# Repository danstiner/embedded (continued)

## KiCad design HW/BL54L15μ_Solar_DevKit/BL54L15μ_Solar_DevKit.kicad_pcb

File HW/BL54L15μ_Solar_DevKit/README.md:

## BOM

+------------------+-----+--------------------+-----------------------------------------+---------------------------------------------------------------------+
|    Reference     | Qty |       Value        |               Part Number               |                              Footprint                              |
+------------------+-----+--------------------+-----------------------------------------+---------------------------------------------------------------------+
| C1,C5            |   2 | 1μF                | CL05A105KA5NQNC                         | Capacitor_SMD:C_0402_1005Metric                                     |
| C2,C4,C7,C10,C11 |   5 | 10μF               | CL10A106KP8NNNC                         | Capacitor_SMD:C_0603_1608Metric                                     |
| C3               |   1 | 10uF               | CL10A106KP8NNNC                         | Capacitor_SMD:C_0603_1608Metric                                     |
| C6               |   1 | 2.2μF              | CL05A225KP5NSNC                         | Capacitor_SMD:C_0402_1005Metric                                     |
| C8,C9            |   2 | 1μF                | CL10A105KP8NNNC                         | Capacitor_SMD:C_0603_1608Metric                                     |
| C12              |   1 | 100nF              | CL05B103KB5NNNC                         | Capacitor_SMD:C_0402_1005Metric                                     |
| D1               |   1 | PWRLED             | 150060GS75000                           | LED_SMD:LED_0603_1608Metric                                         |
| D2               |   1 | PWRLED             | 150060SS75000                           | LED_SMD:LED_0603_1608Metric                                         |
| D3               |   1 | WL-SFTW_3528_PLCC6 | 150352M173300                           | 150352M173300:WL-SFTW_3528_PLCC6                                    |
| IC1              |   1 | nrf54L 453-00223R  | 453-00223R                              | Ezurio 453-00223R:45300223R                                         |
| J1               |   1 | Conn_Qwiic_1       | BM04B-SRSS-TB                           | Connector_JST:JST_SH_BM04B-SRSS-TB_1x04-1MP_P1.00mm_Vertical        |
| J2               |   1 | USB_C_Receptacle   | USB4056-03-A                            | USB4056_03_A:GCT_USB4056-03-A_REVA2                                 |
| J3,J4            |   2 | Conn_01x12_Pin     |                                         | Connector_PinHeader_2.54mm_SilkFree:PinHeader_1x12_P2.54mm_Vertical |
| J5               |   1 | Conn_01x02         |                                         | Connector_PinHeader_2.54mm:PinHeader_1x03_P2.54mm_Vertical          |
| J6,J7            |   2 | Conn_01x02         | B2B-PH-K-S                              | Connector_JST:JST_PH_B2B-PH-K_1x02_P2.00mm_Vertical                 |
| J8               |   1 | Conn_Qwiic_2       | BM04B-SRSS-TB                           | Connector_JST:JST_SH_BM04B-SRSS-TB_1x04-1MP_P1.00mm_Vertical        |
| L1,L2            |   2 | 2.2 μH             | CIGT201610EH2R2MNE                      | CIGT201610EH2R2MNE:IND_CIGT2016_SAM                                 |
| R1               |   1 | 2kΩ                | RC0402FR-132KL                          | Resistor_SMD:R_0402_1005Metric                                      |
| R2               |   1 | 250-500 kΩ         | RC0603JR-07330KL                        | Resistor_SMD:R_0603_1608Metric                                      |
| R3               |   1 | 47 kΩ              | RC0603FR-0747KL                         | Resistor_SMD:R_0603_1608Metric                                      |
| R4               |   1 | 100Ω               | RC0603FR-07100RL                        | Resistor_SMD:R_0603_1608Metric                                      |
| SW1              |   1 | Button0            | SKRKAHE020                              | Button_Switch_SMD:SW_Push_SPST_NO_Alps_SKRK                         |
| SW2              |   1 | Reset              | SKRKAHE020                              | Button_Switch_SMD:SW_Push_SPST_NO_Alps_SKRK                         |
| U1               |   1 | NPM1304-QEAA       | NPM1304-QEAA-R7                         | Package_QFN:QFN-32-1EP_5x5mm_P0.5mm_EP3.6x3.6mm_10milThermalVias    |
| X1               |   1 | 32.768 kHz         | CM7V-T1A-LOW-ESR-32.768KHZ-9PF-20-TA-QC | Crystal:Crystal_SMD_2012-2Pin_2.0x1.2mm                             |
+------------------+-----+--------------------+-----------------------------------------+---------------------------------------------------------------------+

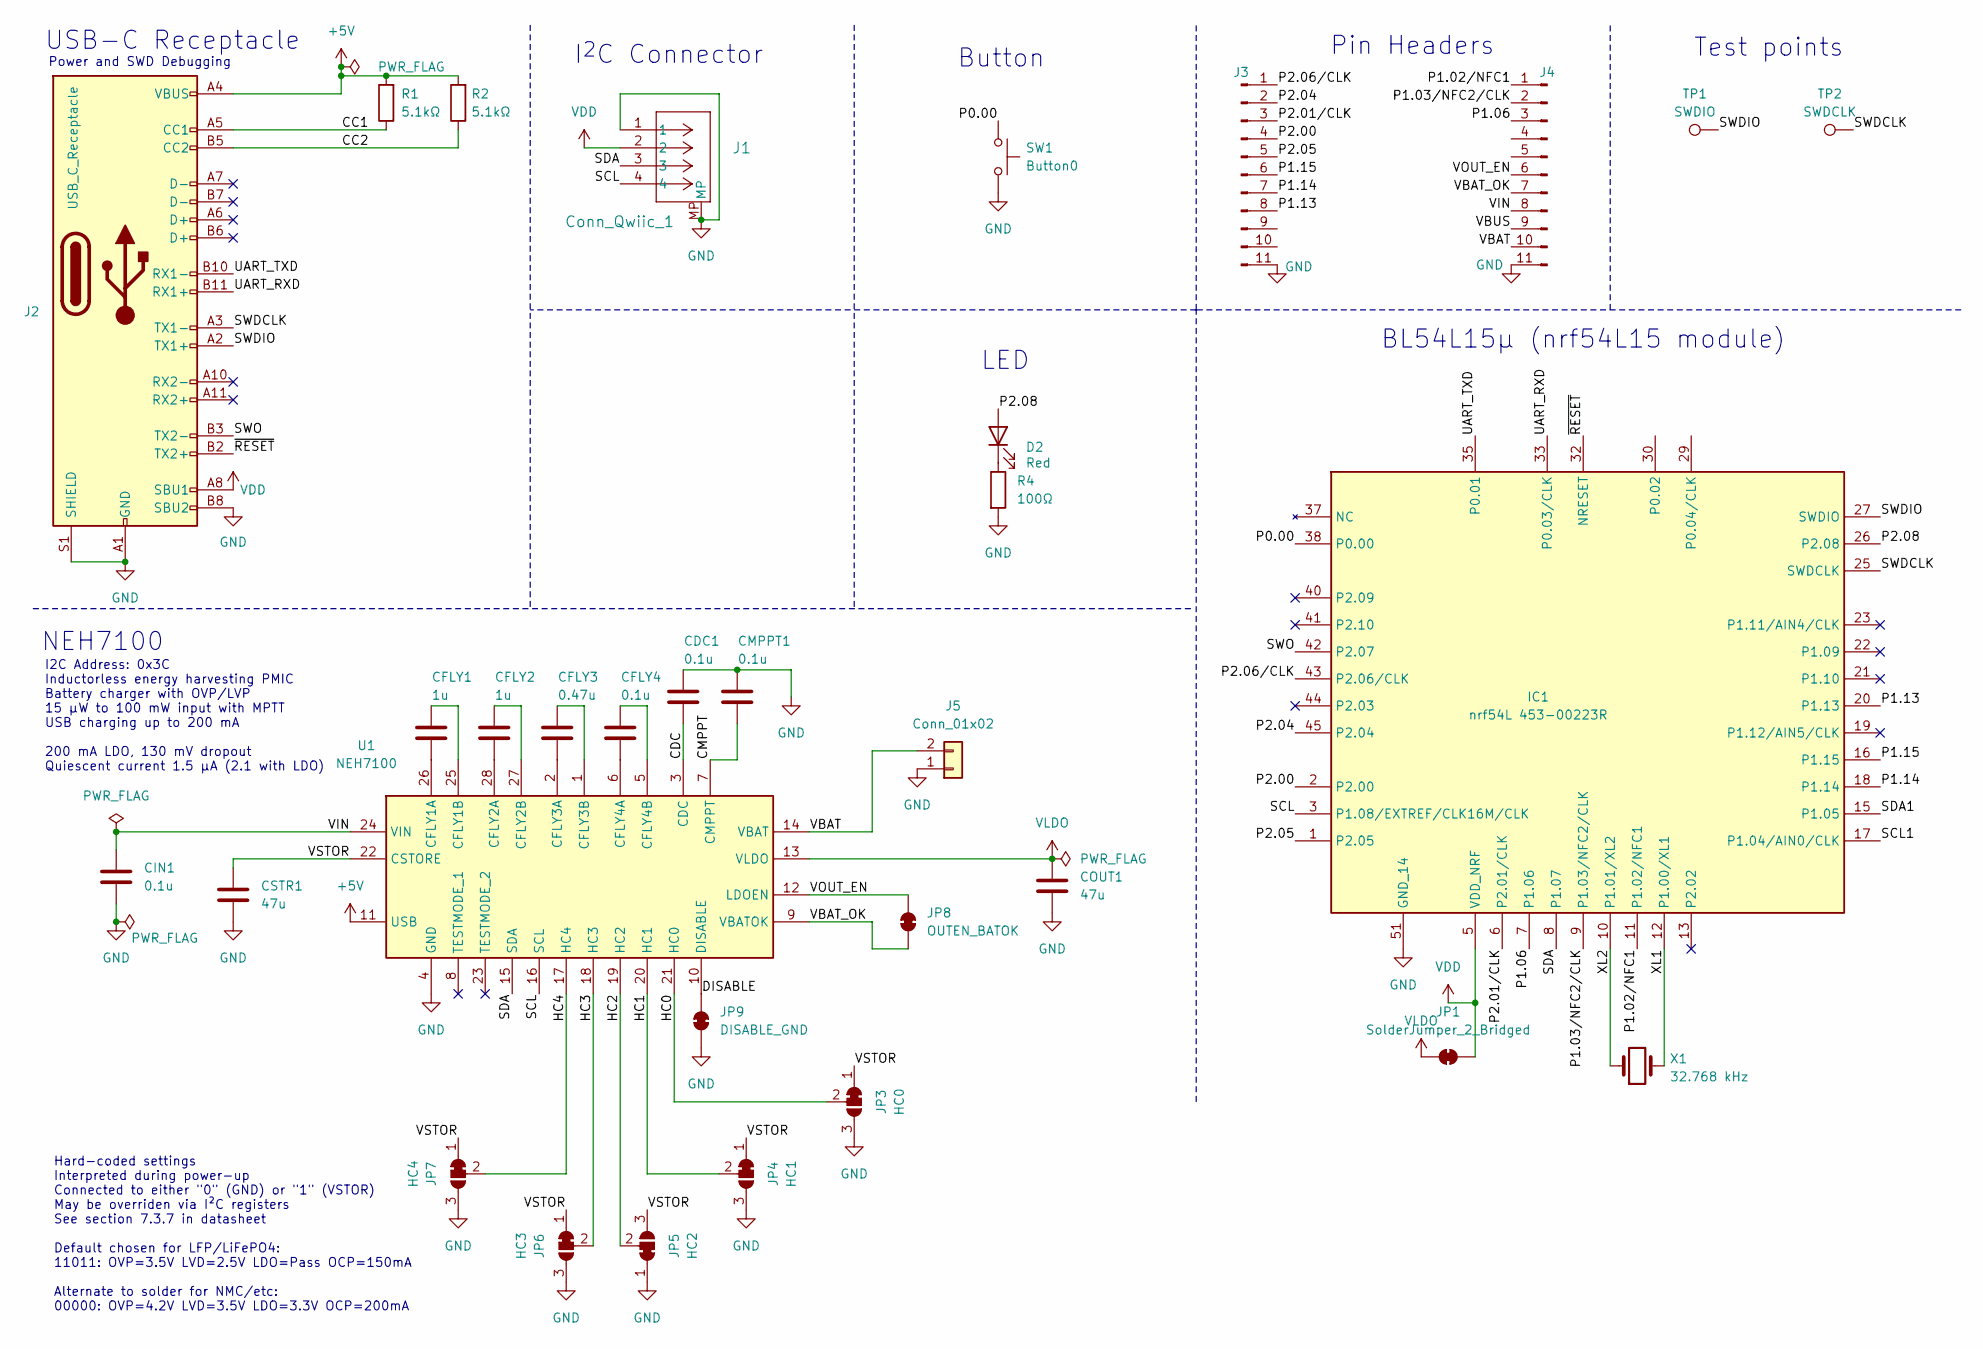
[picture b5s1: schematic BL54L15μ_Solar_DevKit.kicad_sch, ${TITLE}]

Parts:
CDC1: 0.1u; C_0402_1005Metric; Part Number GRM155R61A104KA01J
CFLY1, CFLY2: 1u; C_0402_1005Metric; Part Number GRM153R61A105ME95D
CFLY3: 0.47u; C_0402_1005Metric; Part Number GRM155R61A474KE15D
CFLY4: 0.1u; C_0402_1005Metric; Part Number GRM155R61A104KA01J
CIN1: 0.1u; C_0402_1005Metric; Part Number GRM155R61A104KA01J
CMPPT1: 0.1u; C_0402_1005Metric; Part Number GRM155R61A104KA01J
COUT1: 47u; C_0603_1608Metric; Part Number GRM188R60J476ME15D
CSTR1: 47u; C_0603_1608Metric; Part Number GRM188R60J476ME15D
D2: PWRLED; LED_0603_1608Metric; Part Number 150060SS75000
IC1: nrf54L 453-00223R; 45300223R; Part Number 453-00223R
J1: Conn_Qwiic_1; JST_SH_BM04B-SRSS-TB_1x04-1MP_P1.00mm_Vertical; Part Number BM04B-SRSS-TB
J2: USB_C_Receptacle; GCT_USB4056-03-A_REVA2; Part Number USB4056-03-A
J3, J4: Conn_01x12_Pin; PinHeader_1x11_P2.54mm_Vertical
J5: Conn_01x02; JST_PH_B2B-PH-K_1x02_P2.00mm_Vertical
JP1: SolderJumper_2_Bridged
JP3: HC0; SolderJumper-3_P1.3mm_Bridged12_RoundedPad1.0x1.5mm
JP4: HC1; SolderJumper-3_P1.3mm_Bridged12_RoundedPad1.0x1.5mm
JP5: HC2; SolderJumper-3_P1.3mm_Bridged12_RoundedPad1.0x1.5mm
JP6: HC3; SolderJumper-3_P1.3mm_Bridged12_RoundedPad1.0x1.5mm
JP7: HC4; SolderJumper-3_P1.3mm_Bridged12_RoundedPad1.0x1.5mm
JP8: OUTEN_BATOK; SolderJumper-2_P1.3mm_Bridged_RoundedPad1.0x1.5mm
JP9: DISABLE_GND; SolderJumper-2_P1.3mm_Bridged_RoundedPad1.0x1.5mm
R1, R2: 5.1kΩ
R4: 100Ω; R_0603_1608Metric; Part Number RC0603FR-07100RL
SW1: Button0; SW_Push_SPST_NO_Alps_SKRK; Part Number SKRKAHE020; Digikey Part Number 4809-SKRKAHE020CT-ND
TP1: SWDIO; TestPoint_Pad_D1.0mm
TP2: SWDCLK; TestPoint_Pad_D1.0mm
U1: NEH7100; QFN40P400X400X90-29N-D; Mouser Part Number 771-NEH7100BUHP
X1: 32.768 kHz; Crystal_SMD_2012-2Pin_2.0x1.2mm; Part Number CM7V-T1A-LOW-ESR-32.768KHZ-9PF-20-TA-QC

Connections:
+5V: J2.A4 (VBUS), J2.A9 (VBUS), J2.B4 (VBUS), J2.B9 (VBUS), R1.2, R2.2, U1.11 (USB)
/CC1: J2.A5 (CC1), R1.1
/CC2: J2.B5 (CC2), R2.1
/CDC: CDC1.2, U1.3 (CDC)
/CMPPT: CMPPT1.2, U1.7 (CMPPT)
/DISABLE: JP9.2 (B), U1.10 (DISABLE)
/HC0: JP3.2 (C), U1.21 (HC0)
/HC1: JP4.2 (C), U1.20 (HC1)
/HC2: JP5.2 (C), U1.19 (HC2)
/HC3: JP6.2 (C), U1.18 (HC3)
/HC4: JP7.2 (C), U1.17 (HC4)
/P0.00: IC1.38 (P0.00), SW1.1
/P1.02/NFC1: IC1.11 (P1.02/NFC1), J4.1
/P1.03/NFC2/CLK: IC1.9 (P1.03/NFC2/CLK), J4.2
/P1.06: IC1.7 (P1.06), J4.3
/P1.13: IC1.20 (P1.13), J3.8
/P1.14: IC1.18 (P1.14), J3.7
/P1.15: IC1.16 (P1.15), J3.6
/P2.00: IC1.2 (P2.00), J3.4
/P2.01/CLK: IC1.6 (P2.01/CLK), J3.3
/P2.04: IC1.45 (P2.04), J3.2
/P2.05: IC1.1 (P2.05), J3.5
/P2.06/CLK: IC1.43 (P2.06/CLK), J3.1
/P2.08: D2.2 (A), IC1.26 (P2.08)
/SCL: IC1.3 (P1.08/EXTREF/CLK16M/CLK), J1.4, U1.16 (SCL)
/SCL1: IC1.17 (P1.04/AIN0/CLK)
/SCL2: IC1.29 (P0.04/CLK)
/SDA: IC1.8 (P1.07), J1.3, U1.15 (SDA)
/SDA1: IC1.15 (P1.05)
/SDA2: IC1.30 (P0.02)
/SWDCLK: IC1.25 (SWDCLK), J2.A3 (TX1-), TP2.1
/SWDIO: IC1.27 (SWDIO), J2.A2 (TX1+), TP1.1
/SWO: IC1.42 (P2.07), J2.B3 (TX2-)
/VBAT: J4.10, J5.2, U1.14 (VBAT)
/VBAT_OK: J4.7, JP8.1 (A), U1.9 (VBATOK)
/VBUS: J4.9
/VIN: CIN1.1, J4.8, U1.24 (VIN)
/VOUT_EN: J4.6, JP8.2 (B), U1.12 (LDOEN)
/VSTOR: CSTR1.1, JP3.1 (A), JP4.1 (A), JP5.3 (B), JP6.1 (A), JP7.1 (A), U1.22 (CSTORE)
/XL1: IC1.12 (P1.00/XL1), X1.2
/XL2: IC1.10 (P1.01/XL2), X1.1
/~RESET: IC1.32 (NRESET), J2.B2 (TX2+)
GND: CDC1.1, CIN1.2, CMPPT1.1, COUT1.2, CSTR1.2, IC1.4 (GND_1), IC1.14 (GND_2), IC1.24 (GND_3), IC1.28 (GND_4), IC1.31 (GND_5), IC1.34 (GND_6), IC1.36 (GND_7), IC1.39 (GND_8), IC1.46 (GND_9), IC1.47 (GND_10), IC1.48 (GND_11), IC1.49 (GND_12), IC1.50 (GND_13), IC1.51 (GND_14), J1.1, J1.MP, J2.A1 (GND), J2.A12 (GND), J2.B1 (GND), J2.B8 (SBU2), J2.B12 (GND), J2.S1 (SHIELD), J3.11, J4.11, J5.1, JP3.3 (B), JP4.3 (B), JP5.1 (A), JP6.3 (B), JP7.3 (B), JP9.1 (A), R4.2, SW1.2, U1.4 (GND), U1.29 (GND_2)
unnamed: D2.1 (K), R4.1
unnamed: CFLY1.2, U1.26 (CFLY1A)
unnamed: CFLY1.1, U1.25 (CFLY1B)
unnamed: CFLY2.2, U1.28 (CFLY2A)
unnamed: CFLY2.1, U1.27 (CFLY2B)
unnamed: CFLY3.2, U1.2 (CFLY3A)
unnamed: CFLY3.1, U1.1 (CFLY3B)
unnamed: CFLY4.2, U1.6 (CFLY4A)
unnamed: CFLY4.1, U1.5 (CFLY4B)
VDD: IC1.5 (VDD_NRF), J1.2, J2.A8 (SBU1), JP1.2 (B)
VLDO: COUT1.1, JP1.1 (A), U1.13 (VLDO)

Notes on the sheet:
I2C Address: 0x3C Inductorless energy harvesting PMIC Battery charger with OVP/LVP 15 μW to 100 mW input with MPTT USB charging up to 200 mA 200 mA LDO, 130 mV dropout Quiescent current 1.5 μA (2.1 with LDO)
I^{2}C Connector
USB-C Receptacle
Button
BL54L15μ (nrf54L15 module)
Test points
Pin Headers
Power and SWD Debugging
LED
NEH7100
Hard-coded settings Interpreted during power-up Connected to either "0" (GND) or "1" (VSTOR) May be overriden via I²C registers See section 7.3.7 in datasheet Default chosen for LFP/LiFePO4: 11011: OVP=3.5V LVD=2.5V LDO=Pass OCP=150mA Alternate to solder for NMC/etc: 00000: OVP=4.2V LVD=3.5V LDO=3.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

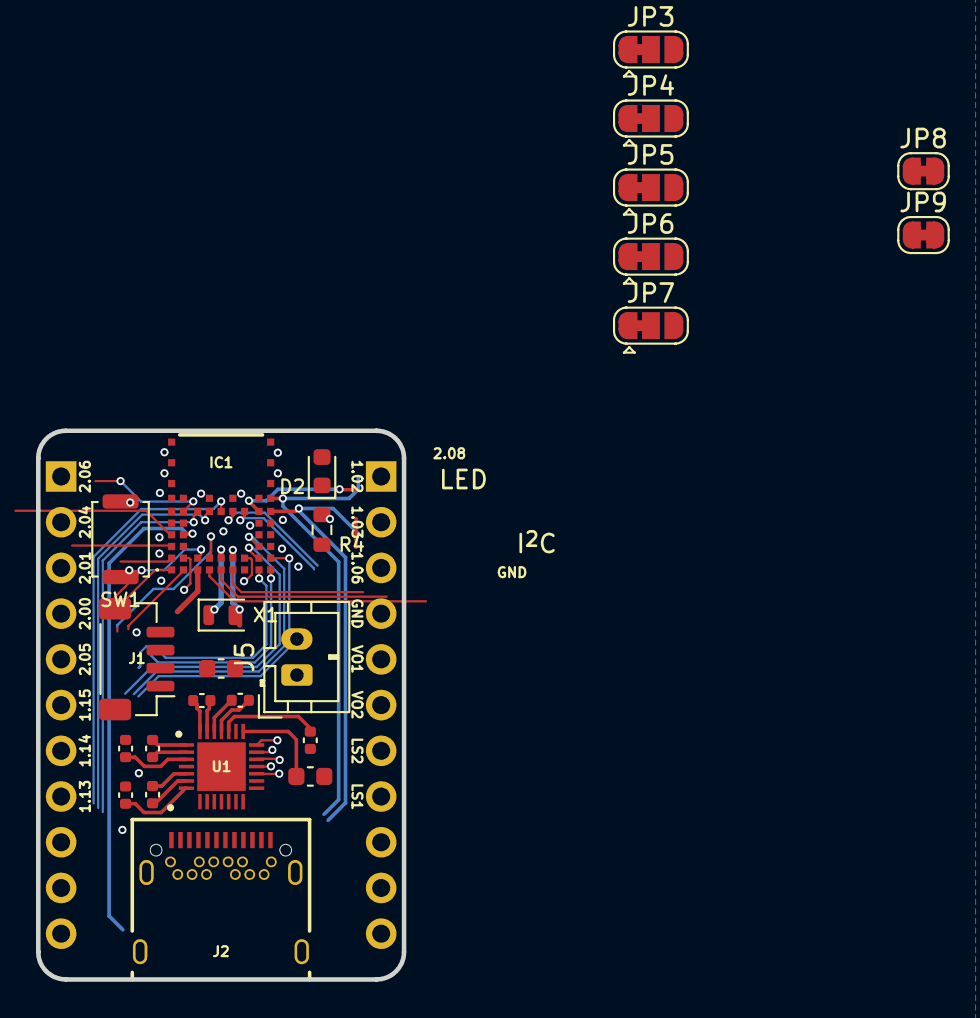
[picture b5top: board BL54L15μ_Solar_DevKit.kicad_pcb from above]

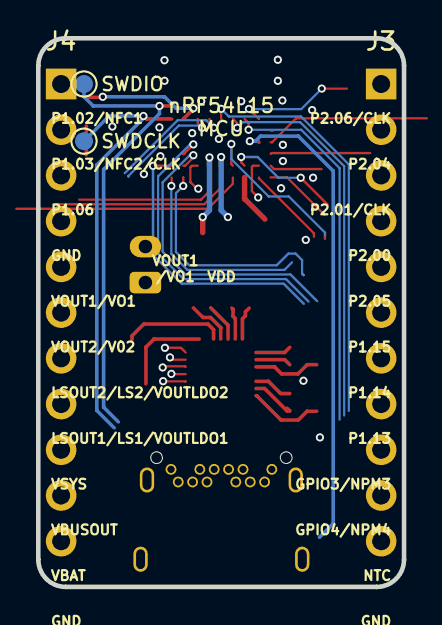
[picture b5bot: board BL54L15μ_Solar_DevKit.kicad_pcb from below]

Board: 4 copper layers, 20.3 x 30.5 mm, 29 parts (4 on the bottom side), 47 nets.

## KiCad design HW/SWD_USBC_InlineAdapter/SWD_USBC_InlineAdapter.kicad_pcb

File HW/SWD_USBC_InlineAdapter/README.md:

## Bill of materials

+-----------+-----+----------------------+--------------------+------------------------------------------------------------------------+
| Reference | Qty | Value                | Part Number        | Footprint                                                              |
+-----------+-----+----------------------+--------------------+------------------------------------------------------------------------+
| D1        | 1   | RED LED              | 150060SS75000      | Diode_SMD:D_0603_1608Metric                                            |
| J1        | 1   | Conn_ARM_JTAG_SWD_10 | FTSH-105-01-F-DV-K | Connector_PinHeader_1.27mm:PinHeader_2x05_P1.27mm_Vertical_SMD         |
| J2        | 1   | Conn_01x04           | 0532610471         | Connector_Molex:Molex_PicoBlade_53261-0471_1x04-1MP_P1.25mm_Horizontal |
| J3        | 1   | USB_C_Receptacle     | USB4056-03-A       | USB4056_03_A:GCT_USB4056-03-A_REVA2                                    |
| P1        | 1   | USB_C_Plug           | USB4155-03-C       | USB4155_03_C:GCT_USB4155-03-C_REVA                                     |
| R1        | 1   | 100Ω                 | RC0603FR-07100RL   | Resistor_SMD:R_0603_1608Metric                                         |
| R2        | 1   | 22kΩ ±5%             | RC0603FR-1322KL    | Resistor_SMD:R_0603_1608Metric                                         |
| R3        | 1   | 10kΩ ±5%             | RC0603FR-0710KL    | Resistor_SMD:R_0603_1608Metric                                         |
| R4,R5     | 2   | 5.1k                 | RC0603FR-075K1L    | Resistor_SMD:R_0603_1608Metric                                         |
+-----------+-----+----------------------+--------------------+------------------------------------------------------------------------+

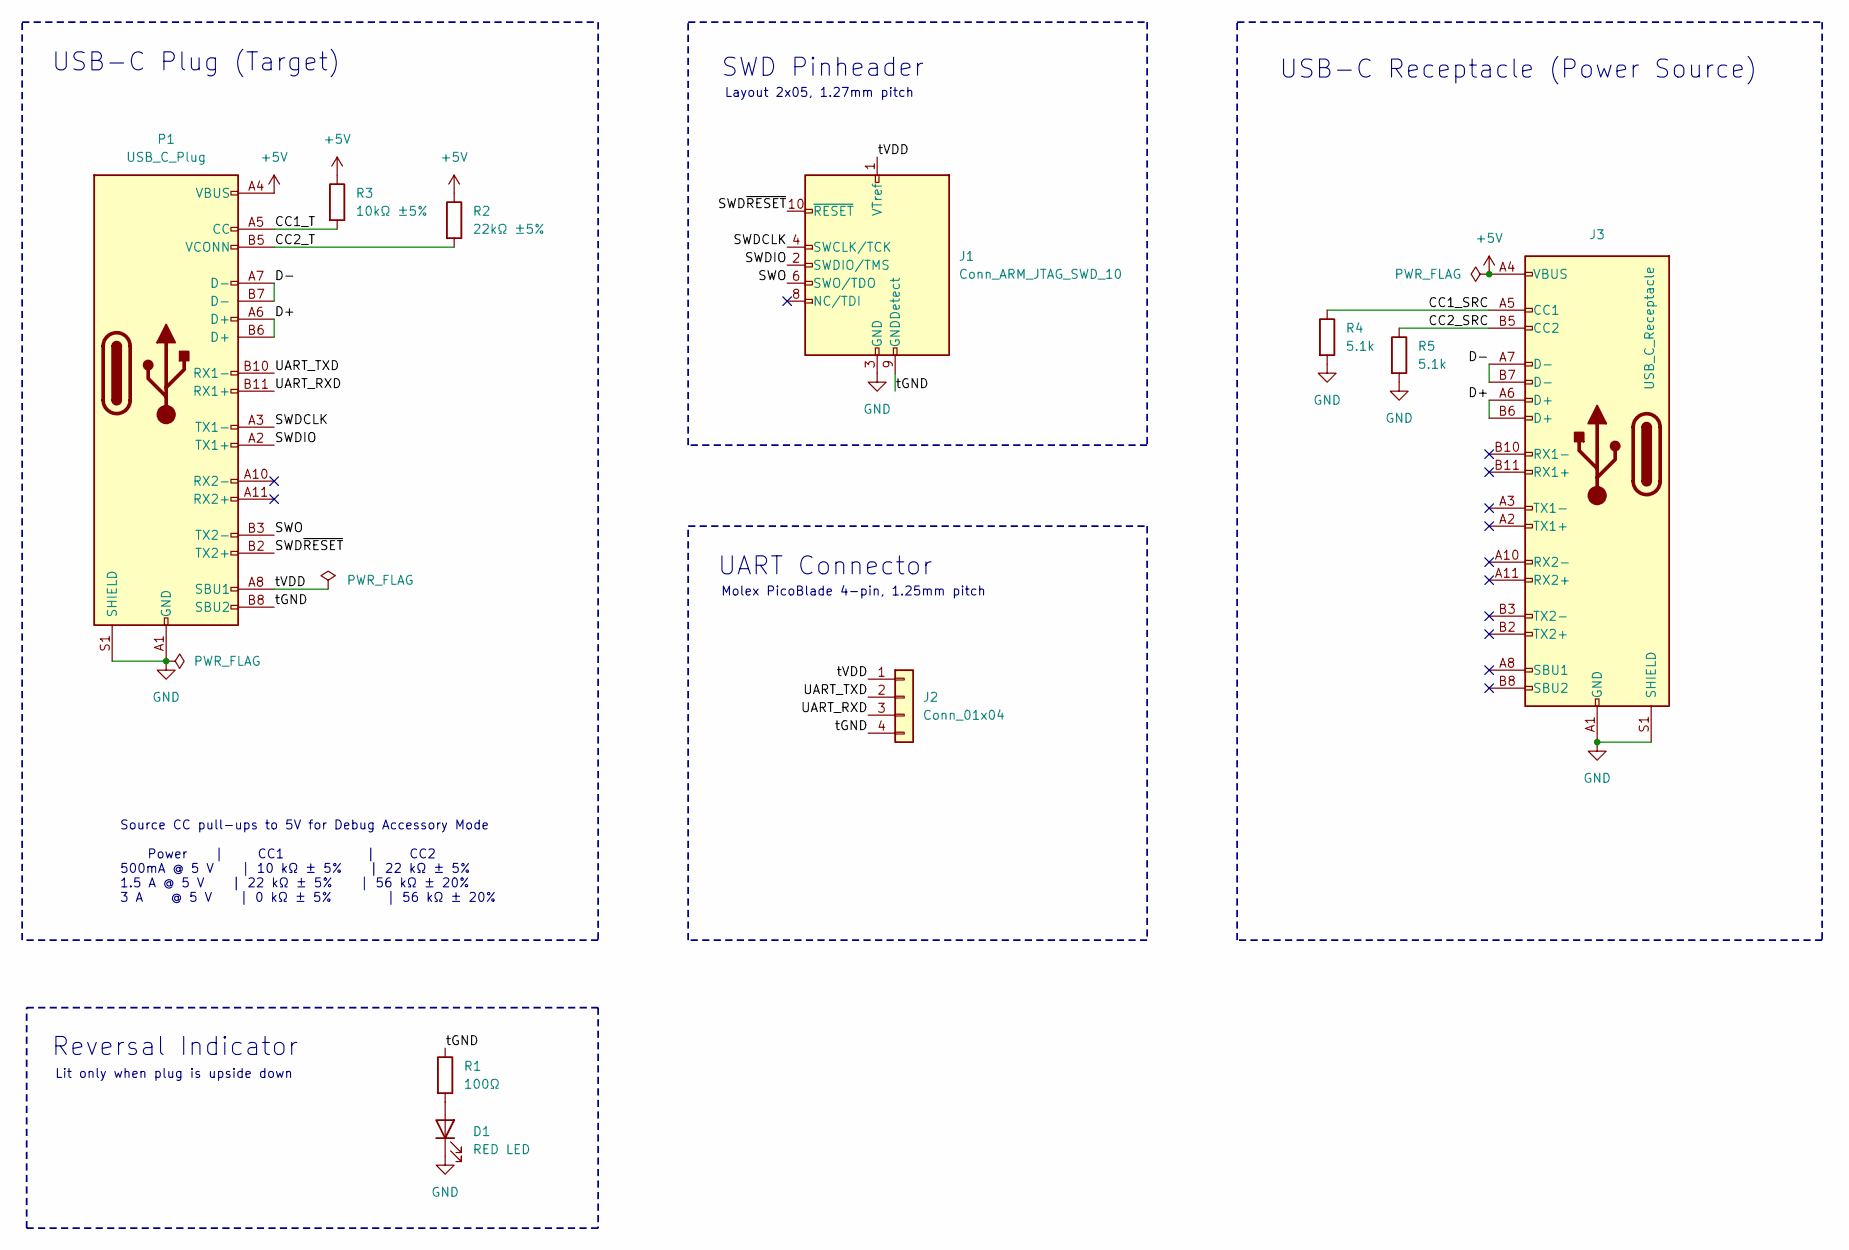
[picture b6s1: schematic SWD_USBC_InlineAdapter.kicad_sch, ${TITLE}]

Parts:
D1: RED LED; D_0603_1608Metric; Part Number 150060SS75000
J1: Conn_ARM_JTAG_SWD_10; PinHeader_2x05_P1.27mm_Vertical_SMD; Part Number FTSH-105-01-F-DV-K
J2: Conn_01x04; Molex_PicoBlade_53261-0471_1x04-1MP_P1.25mm_Horizontal; Part Number 0532610471
J3: USB_C_Receptacle; GCT_USB4056-03-A_REVA2; Part Number USB4056-03-A
P1: USB_C_Plug; GCT_USB4155-03-C_REVA; Part Number USB4155-03-C
R1: 100Ω; R_0603_1608Metric; Part Number RC0603FR-07100RL
R2: 22kΩ ±5%; R_0603_1608Metric; Digikey Part Number RC0603FR-1322KL
R3: 10kΩ ±5%; R_0603_1608Metric; Digikey Part Number RC0603FR-0710KL
R4, R5: 5.1k; R_0603_1608Metric; Digikey Part Number 311-5.10KHRCT-ND

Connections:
+5V: J3.A4 (VBUS), J3.A9 (VBUS), J3.B4 (VBUS), J3.B9 (VBUS), P1.A4 (VBUS), P1.A9 (VBUS), P1.B4 (VBUS), P1.B9 (VBUS), R2.1, R3.1
/CC1_SRC: J3.A5 (CC1), R4.1
/CC1_T: P1.A5 (CC), R3.2
/CC2_SRC: J3.B5 (CC2), R5.1
/CC2_T: P1.B5 (VCONN), R2.2
/D+: J3.A6 (D+), J3.B6 (D+), P1.A6 (D+), P1.B6 (D+)
/D-: J3.A7 (D-), J3.B7 (D-), P1.A7 (D-), P1.B7 (D-)
/SWDCLK: J1.4 (SWCLK/TCK), P1.A3 (TX1-)
/SWDIO: J1.2 (SWDIO/TMS), P1.A2 (TX1+)
/SWD~RESET: J1.10 (~RESET), P1.B2 (TX2+)
/SWO: J1.6 (SWO/TDO), P1.B3 (TX2-)
/UART_RXD: J2.3, P1.B11 (RX1+)
/UART_TXD: J2.2, P1.B10 (RX1-)
/tGND: J1.9 (GNDDetect), J2.4, P1.B8 (SBU2), R1.1
/tVDD: J1.1 (VTref), J2.1, P1.A8 (SBU1)
GND: D1.1 (K), J1.3 (GND), J1.5 (GND), J3.A1 (GND), J3.A12 (GND), J3.B1 (GND), J3.B12 (GND), J3.S1 (SHIELD), P1.A1 (GND), P1.A12 (GND), P1.B1 (GND), P1.B12 (GND), P1.S1 (SHIELD), R4.2, R5.2
unnamed: D1.2 (A), R1.2

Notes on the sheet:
SWD Pinheader
Layout 2x05, 1.27mm pitch
Reversal Indicator
Lit only when plug is upside down
USB-C Receptacle (Power Source)
Source CC pull-ups to 5V for Debug Accessory Mode Power | CC1 | CC2 500mA @ 5 V | 10 kΩ ± 5% | 22 kΩ ± 5% 1.5 A @ 5 V | 22 kΩ ± 5% | 56 kΩ ± 20% 3 A @ 5 V | 0 kΩ ± 5% | 56 kΩ ± 20%
USB-C Plug (Target)
UART Connector
Molex PicoBlade 4-pin, 1.25mm pitch

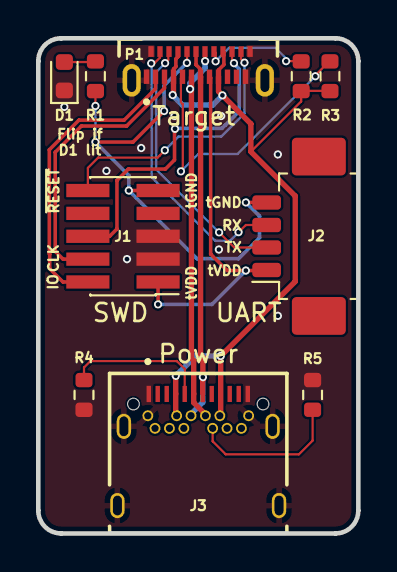
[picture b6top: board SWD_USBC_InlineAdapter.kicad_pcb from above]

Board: 4 copper layers, 17.8 x 27.5 mm, 10 parts (0 on the bottom side), 17 nets.

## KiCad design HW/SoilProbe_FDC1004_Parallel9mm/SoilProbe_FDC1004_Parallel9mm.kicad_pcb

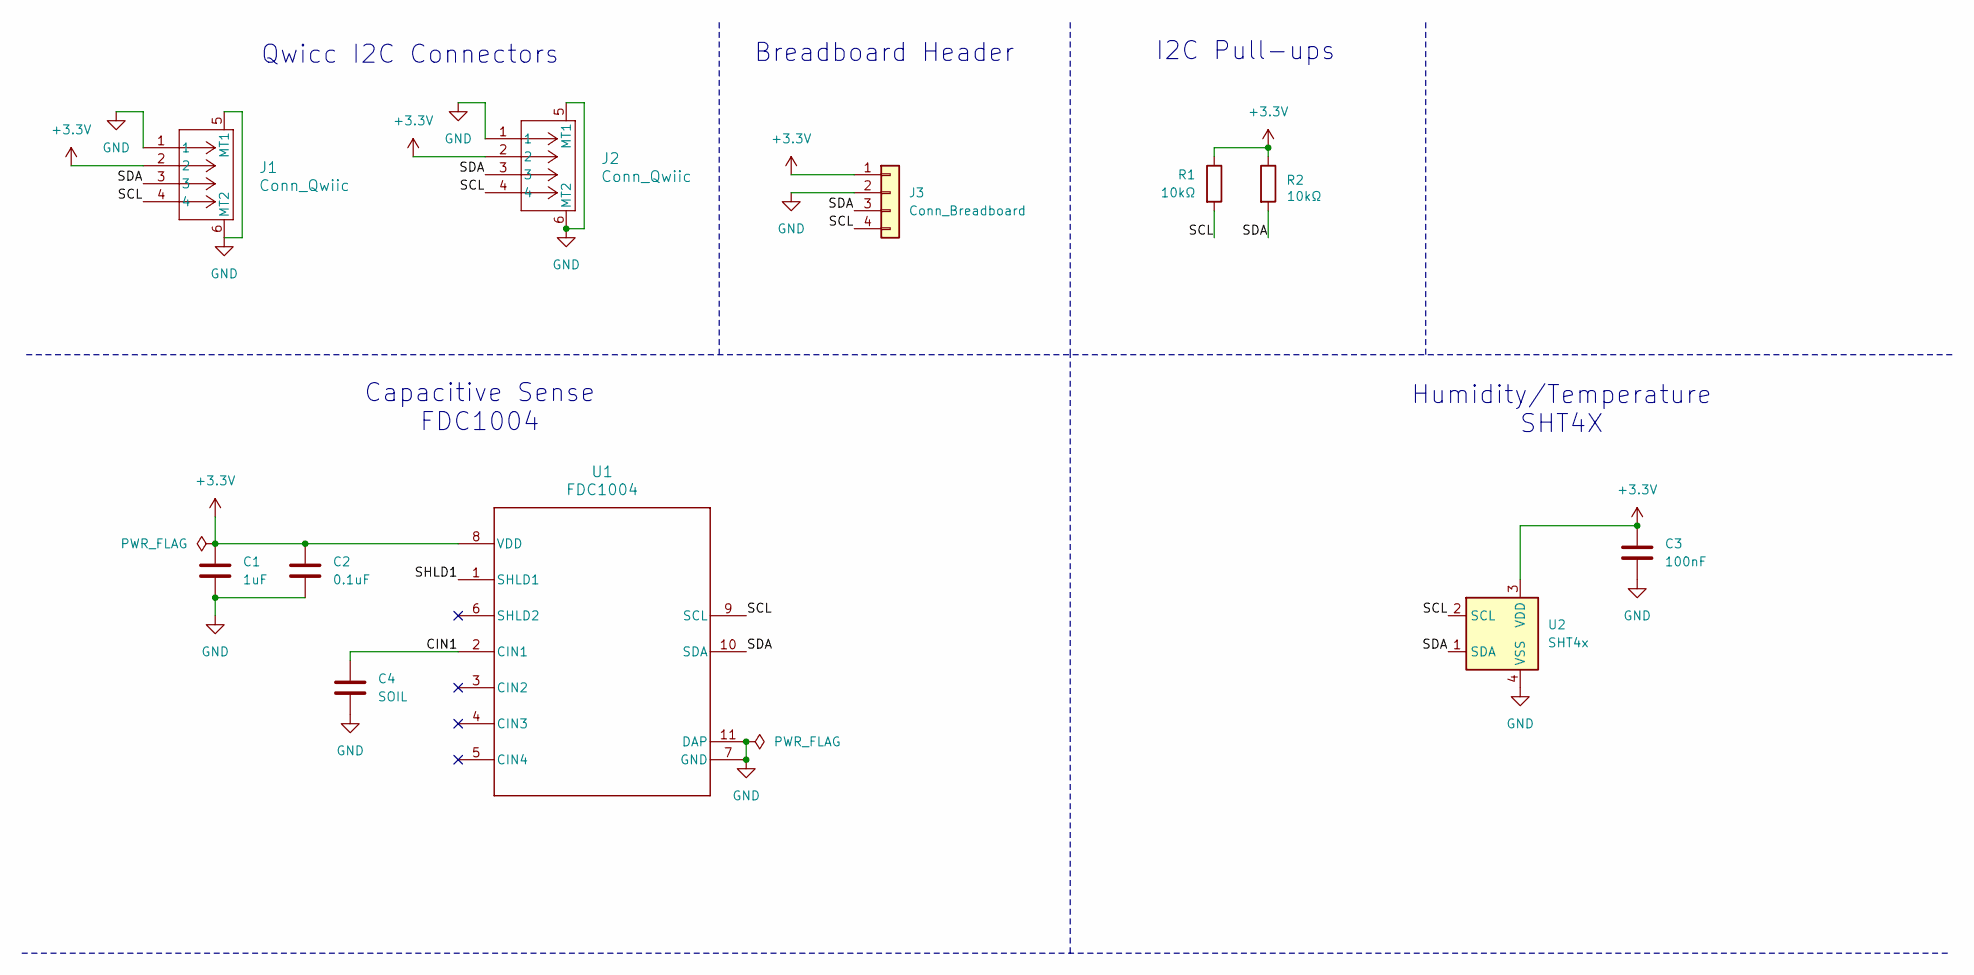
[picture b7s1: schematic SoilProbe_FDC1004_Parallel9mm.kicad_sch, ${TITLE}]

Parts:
C1: 1uF; C_0603_1608Metric; Manufacturer Part Number CL10A105KP8NNNC
C2: 0.1uF; C_0402_1005Metric; Manufacturer Part Number GRM155R61A104KA01J
C3: 100nF; C_0402_1005Metric; Part Number GRM155R61A104KA01J
C4: SOIL; C_Rectangle
J1, J2: Conn_Qwiic; CONN_SM04B-SRSS-TB_JST; Manufacturer Part Number SM04B-SRSS-TB; Digikey Part Number 455-SM04B-SRSS-TBCT-ND
J3: Conn_Breadboard; PinHeader_1x04_P2.54mm_Vertical
R1, R2: 10kΩ; R_0603_1608Metric; Manufacturer Part Number RC0603FR-0710KL
U1: FDC1004; DSC0010B_NV; Manufacturer Part Number FDC1004DSCR
U2: SHT4x; Sensirion_DFN-4_1.5x1.5mm_P0.8mm_SHT4x_NoCentralPad

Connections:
+3.3V: C1.1, C2.1, C3.1, J1.2, J2.2, J3.1, R1.1, R2.1, U1.8 (VDD), U2.3 (VDD)
/CIN1: C4.1, U1.2 (CIN1)
/SCL: J1.4, J2.4, J3.4, R1.2, U1.9 (SCL), U2.2 (SCL)
/SDA: J1.3, J2.3, J3.3, R2.2, U1.10 (SDA), U2.1 (SDA)
/SHLD1: U1.1 (SHLD1)
GND: C1.2, C2.2, C3.2, C4.2, J1.1, J1.5 (MT1), J1.6 (MT2), J2.1, J2.5 (MT1), J2.6 (MT2), J3.2, U1.7 (GND), U1.11 (DAP), U2.4 (VSS)

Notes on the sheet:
Breadboard Header
Qwicc I2C Connectors
Humidity/Temperature SHT4X
Capacitive Sense FDC1004
I2C Pull-ups

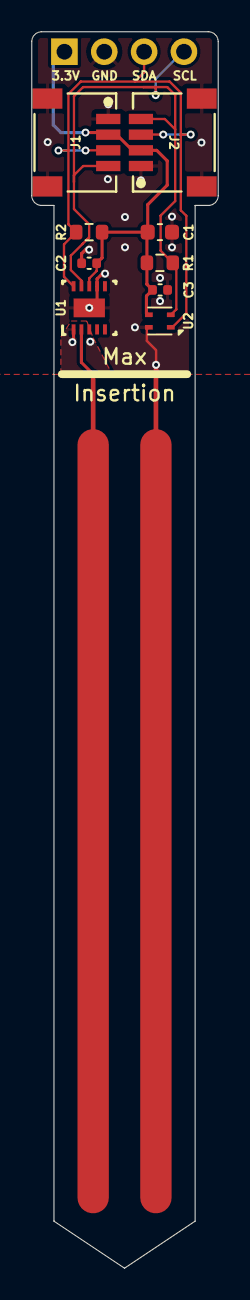
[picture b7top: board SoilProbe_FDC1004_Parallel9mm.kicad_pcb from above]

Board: 2 copper layers, 11.9 x 78.8 mm, 11 parts (0 on the bottom side), 5 nets.

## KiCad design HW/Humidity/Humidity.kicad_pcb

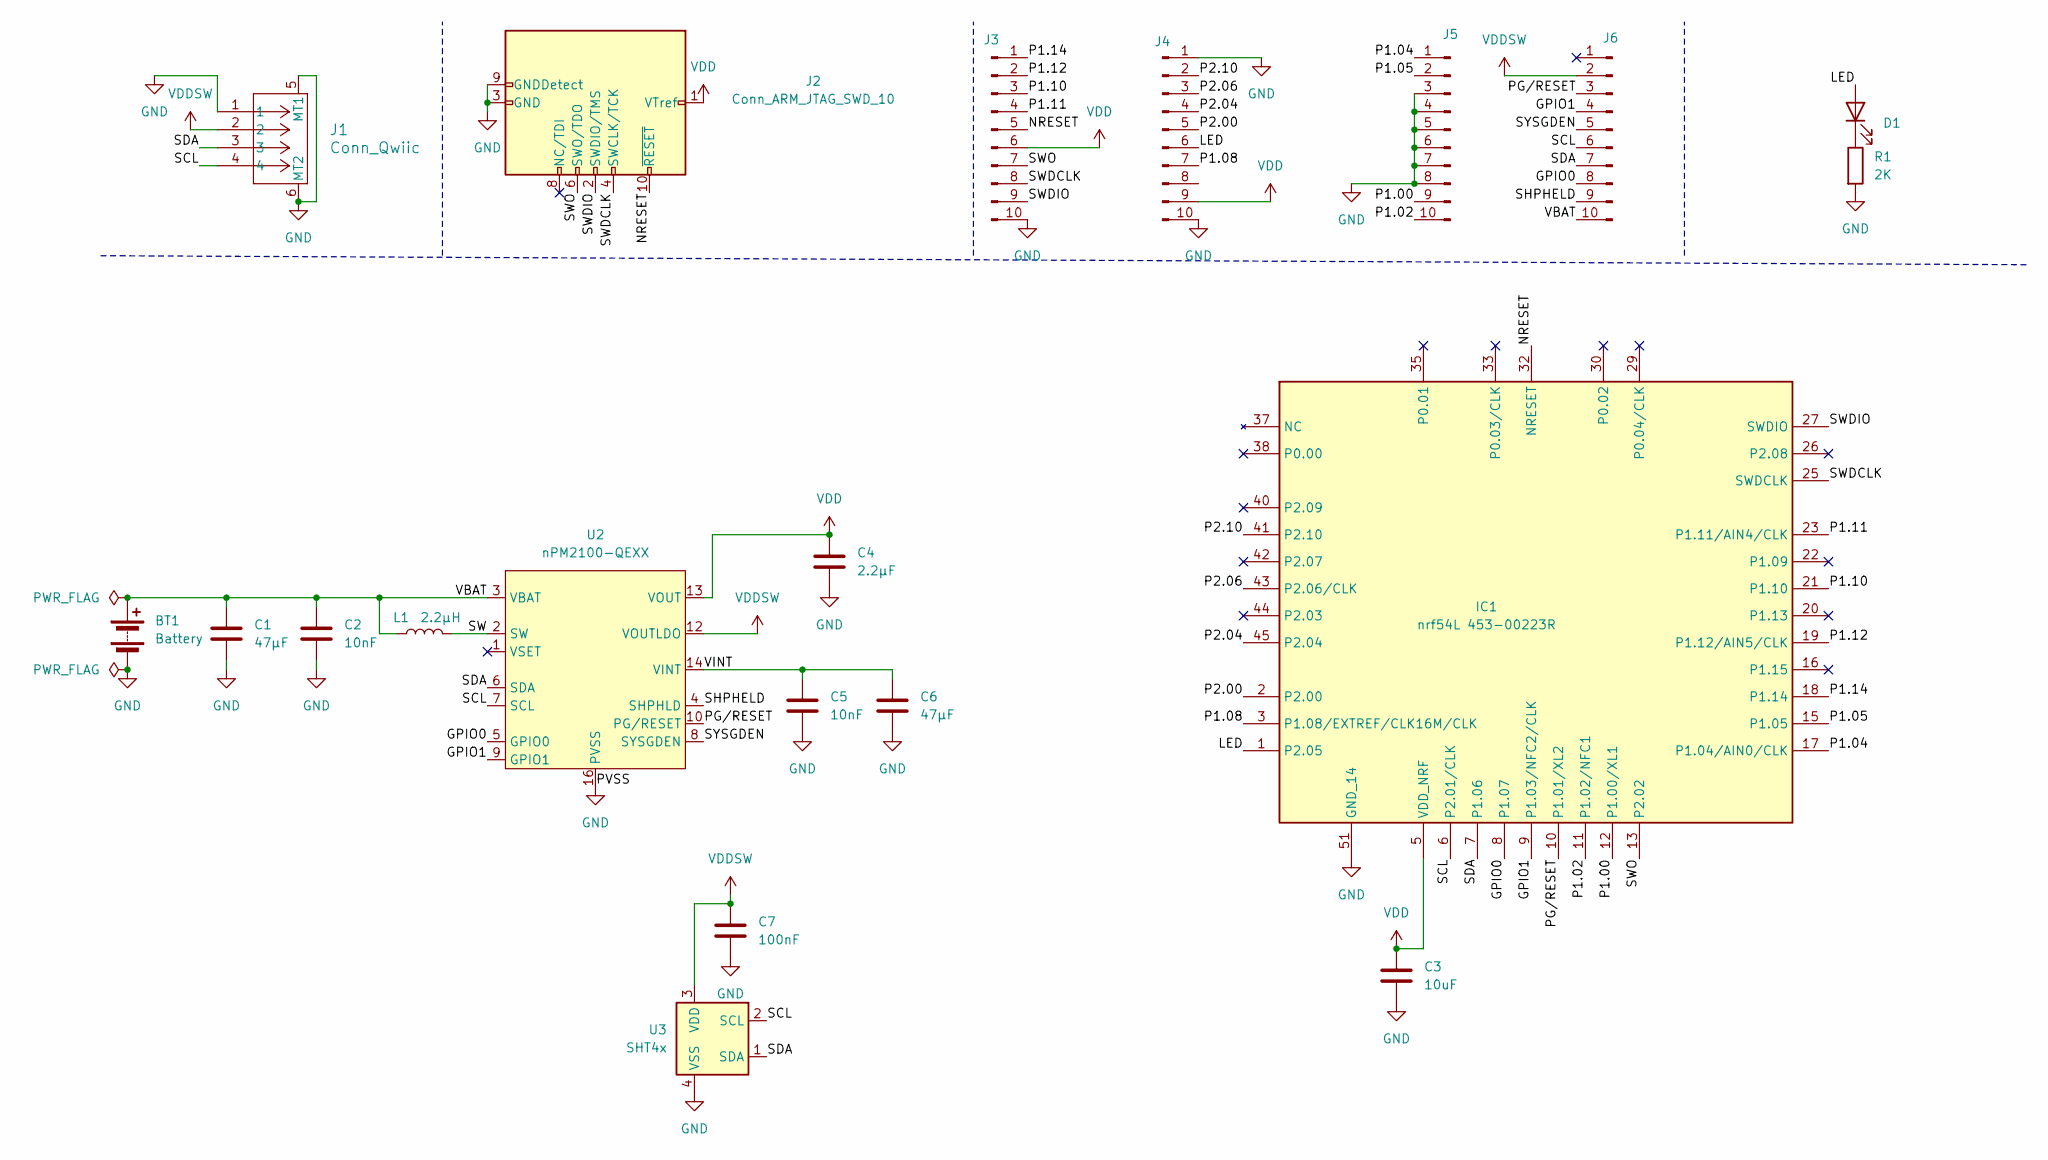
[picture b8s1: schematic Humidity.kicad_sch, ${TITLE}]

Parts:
BT1: Battery; BatteryHolder_Keystone_2468_2xAAA
C1, C6: 47μF; C_0603_1608Metric
C2, C5: 10nF; C_0402_1005Metric
C3: 10uF; C_0603_1608Metric
C4: 2.2μF; C_0402_1005Metric
C7: 100nF; C_0402_1005Metric
D1: PWRLED; LED_0603_1608Metric
IC1: nrf54L 453-00223R; 45300223R; Manufacturer_Part_Number 453-00223R
J1: Conn_Qwiic; CONN_SM04B-SRSS-TB_JST
J2: Conn_ARM_JTAG_SWD_10; PinHeader_2x05_P1.27mm_Vertical_SMD
J3, J4, J5, J6: Conn_01x10_Pin; PinHeader_1x10_P2.54mm_Vertical
L1: 2.2μH; IND_CIGT2016_SAM
R1: 2K; R_0603_1608Metric
U2: nPM2100-QEXX; UQFN-16-1EP_4x4mm_P0.65mm_EP2.6x2.6mm
U3: SHT4x; Sensirion_DFN-4_1.5x1.5mm_P0.8mm_SHT4x_NoCentralPad

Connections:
/GPIO0: IC1.8 (P1.07), J6.8, U2.5 (GPIO0)
/GPIO1: IC1.9 (P1.03/NFC2/CLK), J6.4, U2.9 (GPIO1)
/LED: D1.2 (A), IC1.1 (P2.05), J4.6
/NRESET: IC1.32 (NRESET), J2.10 (~RESET), J3.5
/P1.00: IC1.12 (P1.00/XL1), J5.9
/P1.02: IC1.11 (P1.02/NFC1), J5.10
/P1.04: IC1.17 (P1.04/AIN0/CLK), J5.1
/P1.05: IC1.15 (P1.05), J5.2
/P1.08: IC1.3 (P1.08/EXTREF/CLK16M/CLK), J4.7
/P1.10: IC1.21 (P1.10), J3.3
/P1.11: IC1.23 (P1.11/AIN4/CLK), J3.4
/P1.12: IC1.19 (P1.12/AIN5/CLK), J3.2
/P1.14: IC1.18 (P1.14), J3.1
/P2.00: IC1.2 (P2.00), J4.5
/P2.04: IC1.45 (P2.04), J4.4
/P2.06: IC1.43 (P2.06/CLK), J4.3
/P2.10: IC1.41 (P2.10), J4.2
/PG/RESET: IC1.10 (P1.01/XL2), J6.3, U2.10 (PG/RESET)
/SCL: IC1.6 (P2.01/CLK), J1.4, J6.6, U2.7 (SCL), U3.2 (SCL)
/SDA: IC1.7 (P1.06), J1.3, J6.7, U2.6 (SDA), U3.1 (SDA)
/SHPHELD: J6.9, U2.4 (SHPHLD)
/SW: L1.2, U2.2 (SW)
/SWDCLK: IC1.25 (SWDCLK), J2.4 (SWCLK/TCK), J3.8
/SWDIO: IC1.27 (SWDIO), J2.2 (SWDIO/TMS), J3.9
/SWO: IC1.13 (P2.02), J2.6 (SWO/TDO), J3.7
/SYSGDEN: J6.5, U2.8 (SYSGDEN)
/VBAT: BT1.1 (+), C1.1, C2.1, J6.10, L1.1, U2.3 (VBAT)
/VINT: C5.1, C6.1, U2.14 (VINT), U2.15 (VINT)
GND: BT1.2 (-), C1.2, C2.2, C3.2, C4.2, C5.2, C6.2, C7.2, IC1.4 (GND_1), IC1.14 (GND_2), IC1.24 (GND_3), IC1.28 (GND_4), IC1.31 (GND_5), IC1.34 (GND_6), IC1.36 (GND_7), IC1.39 (GND_8), IC1.46 (GND_9), IC1.47 (GND_10), IC1.48 (GND_11), IC1.49 (GND_12), IC1.50 (GND_13), IC1.51 (GND_14), J1.1, J1.5 (MT1), J1.6 (MT2), J2.3 (GND), J2.5 (GND), J2.9 (GNDDetect), J3.10, J4.1, J4.10, J5.3, J5.4, J5.5, J5.6, J5.7, J5.8, R1.2, U2.11 (AVSS2), U2.16 (PVSS), U2.17 (EP), U3.4 (VSS)
unnamed: D1.1 (K), R1.1
VDD: C3.1, C4.1, IC1.5 (VDD_NRF), J2.1 (VTref), J3.6, J4.9, U2.13 (VOUT)
VDDSW: C7.1, J1.2, J6.2, U2.12 (VOUTLDO), U3.3 (VDD)

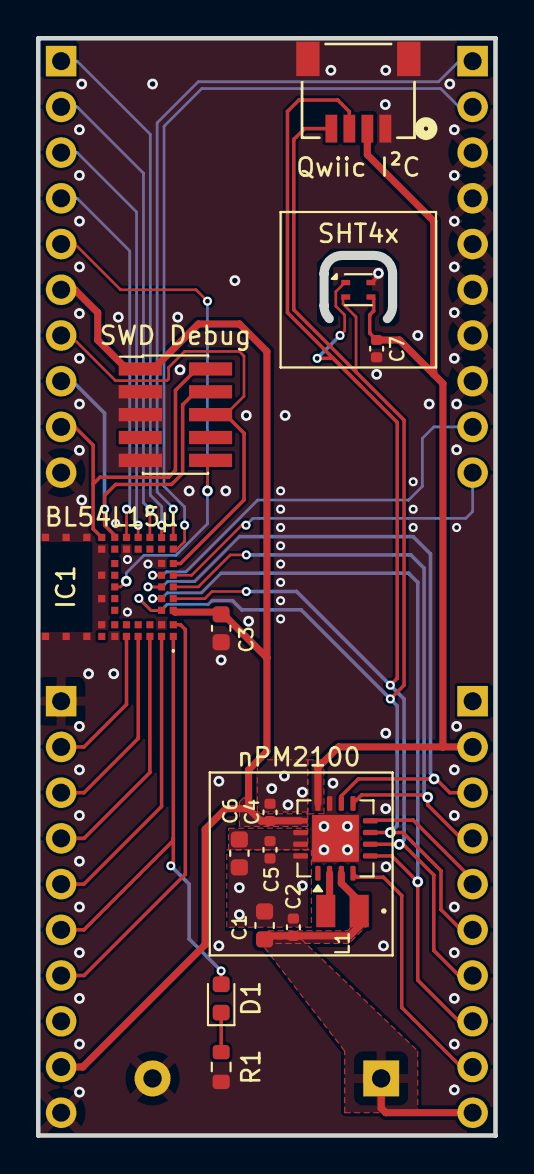
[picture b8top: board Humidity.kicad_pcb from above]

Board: 2 copper layers, 25.4 x 61.0 mm, 20 parts (1 on the bottom side), 32 nets.

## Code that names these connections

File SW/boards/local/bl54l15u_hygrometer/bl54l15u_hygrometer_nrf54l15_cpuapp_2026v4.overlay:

/*
 * BL54L15u Hygrometer — 2026v4 board revision
 *
 * Differences from the base 2026v3 devicetree:
 *   - No PMIC: runs directly off a CR2 cell.
 *   - No BME688 / STCC4, single I2C bus.
 *   - No status LED.
 *   - Adds a resistive leak sensor: LEAK_DRIVE=P0.01, LEAK_SENSE=P1.07.
 *   - Adds a buzzer/siren on P2.05 (driven via Q1)
 *
 * The base DTS keeps SHT4x on I2C21 (SDA=P1.14, SCL=P1.04), unchanged here.
 */

#include <zephyr/dt-bindings/adc/adc.h>
#include <zephyr/dt-bindings/adc/nrf-saadc.h>
#include <zephyr/dt-bindings/gpio/gpio.h>

/* ---- Remove 2026v3-only hardware ---- */

/* No nPM2100 PMIC on v4. Disable the PMIC and each of its child devices
 * individually — a node's own status is not inherited from its parent, so the
 * regulator/vbat/watchdog children would otherwise still report "okay" and the
 * firmware would pick the PMIC battery path instead of the SAADC one. */
&npm2100_pmic {
	status = "disabled";
};

&npm2100_ldsw {
	status = "disabled";
};

&npm2100_vbat {
	status = "disabled";
};

&npm2100_wdt {
	status = "disabled";
};

/* No BME688 / STCC4 and no I2C20 bus on v4 */
&bme688 {
	status = "disabled";
};

&i2c20 {
	status = "disabled";
};

/* No status LED on v4. Disable the child too (status is not inherited) so the
 * boot_led alias resolves as not-okay and the boot-LED code is skipped. */
&leds {
	status = "disabled";
};

&red_led {
	status = "disabled";
};

/* ---- Add 2026v4 hardware ---- */

/* P0.01 (LEAK_DRIVE) lives on gpio0; P2.05 (buzzer) on gpio2.
 * gpio1 (SHT4x I2C, leak sense) is already enabled by the base DTS. */
&gpio0 {
	status = "okay";
};

&gpio2 {
	status = "okay";
};

/* SAADC: CR2 battery-voltage measurement (channel@0, internal VDD) and the
 * leak-sense divider (channel@1, AIN3 / P1.07; see leak-sensor below). */
&adc {
	status = "okay";
	#address-cells = <1>;
	#size-cells = <0>;

	/* Measure the chip supply (== CR2 voltage). The nRF54L internal reference
	 * is 0.9 V, so 1/4 gain gives a 3.6 V full scale, covering a fresh CR2
	 * (~3.2 V). adc_raw_to_millivolts_dt() does the raw->mV conversion. */
	channel@0 {
		reg = <0>;
		zephyr,gain = "ADC_GAIN_1_4";
		zephyr,reference = "ADC_REF_INTERNAL";
		zephyr,acquisition-time = <ADC_ACQ_TIME_DEFAULT>;
		zephyr,input-positive = <NRF_SAADC_VDD>;
		zephyr,resolution = <12>;
		/* 2^2 = 4x oversampling. The CR2 curve is quite flat; average in
		 * hardware to keep the reported percentage stable. */
		zephyr,oversampling = <2>;
	};

	/* Leak sense divider for LEAK_SENSE. Driven by LEAK_DRIVE at V_bat through
	 * R1+R2+R_water, so 1/4 gain giving a 3.6 V scale covers the full range.
	 * High impedance of R_water and the R3 pull-down (1 MΩ) mean using a long
	 * is high impedance (~R3 ‖ (R1+R2+R_water) ≈ 0.5 MΩ when wet, ~1 MΩ when
	 * acquisition time to let the SAADC S/H settle in dry or damp conditions. */
	channel@1 {
		reg = <1>;
		zephyr,gain = "ADC_GAIN_1_4";
		zephyr,reference = "ADC_REF_INTERNAL";
		zephyr,acquisition-time = <ADC_ACQ_TIME(ADC_ACQ_TIME_MICROSECONDS, 40)>;
		zephyr,input-positive = <NRF_SAADC_AIN3>;  /* P1.07 = AIN3 LEAK_SENSE */
		zephyr,resolution = <12>;
	};
};

/ {
	/* Battery voltage source consumed by sensor_reading.cpp via ADC_DT_SPEC_GET */
	vbatt: vbatt {
		compatible = "local,adc-vbatt";
		io-channels = <&adc 0>;
	};

	/* Resistive leak sensor: drive one electrode (via R1 10k), sense the other
	 * (via R2 10k) across the water gap. The board has an external 1M pull-down
	 * (R3) on the sense line, forming the divider:
	 *   V_sense = V_drive * R3 / (R1 + R2 + R_water + R3).
	 * sense-gpios reads the line digitally for an instant wake-on-wet edge;
	 * io-channels samples the same node with the SAADC so a software threshold
	 * can resolve high-resistance damp conditions the digital edge would miss. */
	leak_sensor: leak-sensor {
		compatible = "local,leak-sensor";
		drive-gpios = <&gpio0 1 GPIO_ACTIVE_HIGH>;  /* P0.01 LEAK_DRIVE */
		sense-gpios = <&gpio1 7 GPIO_ACTIVE_HIGH>;  /* P1.07 LEAK_SENSE */
		io-channels = <&adc 1>;                     /* P1.07 = AIN3 */
	};

	/* Buzzer/siren output (P2.05 -> Q1 -> transducer). Reserved for a future
	 * audible-alarm feature; firmware does not drive it yet. Modelled as a
	 * gpio-leds output so the pin has a GPIO_DT_SPEC without a custom binding. */
	buzzer: buzzer {
		compatible = "gpio-leds";
		siren: siren {
			gpios = <&gpio2 5 GPIO_ACTIVE_HIGH>;
			label = "Leak siren";
		};
	};
};
